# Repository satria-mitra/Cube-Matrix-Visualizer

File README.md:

# Cube-Matrix Visualizer

To see how Cube Matrix works, please visit our [youtube channel](https://www.youtube.com/watch?v=XeQNfcWp1Bc)

## What is Cube-Matrix Visualizer?

Cube-Matrix Visualizer creatively connects the fields of IoT (Internet of Things) technology and art, aiming to create a data visualization device that meets the complex needs of contemporary society. Currently, the device focuses on reacting to changes in humidity, temperature and carbon dioxide concentration with a series of artistic LED animations. In the future, the team will provide OTA (over-the-air) services to upgrade the functionality of the device and enable broader data visualization through more captivating animations.

## Why is Cube-Matrix Visualizer Useful? 

In an era oversaturated with data, the Cube-Matrix Visualizer emerges as a beacon of innovation, merging the practicality of IoT technology with the sublime beauty of art. This fusion presents a unique advantage: making data not only accessible but also aesthetically pleasing, transforming mundane statistics into captivating visual stories.

### Artistry and Technology Combined

The Cube-Matrix Visualizer stands apart through its artistic approach to data visualization. Each LED animation is meticulously crafted, not just for clarity, but to evoke emotion and appreciation for the beauty inherent in data. The device acts as a living canvas, where pixels of light paint the ever-changing tapestry of our environment's data.

### Tailored to the Modern Aesthetic

Designed with modern sensibilities in mind, the Cube-Matrix Visualizer is more than a functional device—it's a piece of art that complements any space. Its sleek design and dynamic visual output offer a dual function: enhancing room aesthetics while providing valuable environmental insights. It's an innovative way to integrate technology into our lives without sacrificing style or comfort.

### Engaging Visual Experience

Beyond mere decoration, the Cube-Matrix Visualizer engages its users on a sensory level. The visualizations are designed not only to inform but to mesmerize, creating an immersive experience that turns data observation into a moment of zen. It encourages users to interact with and reflect on their environmental conditions, fostering a deeper connection between the user and their surroundings.

### A Canvas for Future Possibilities

The promise of OTA updates opens a realm of future possibilities, where the device's artistry and functionality evolve together. New data visualizations can be introduced, offering fresh perspectives and insights, and keeping the user's experience vibrant and current. This commitment to growth ensures that the Cube-Matrix Visualizer remains not only a tool for today but a lasting piece of art that continues to enrich lives.

## Market analysis

We are a small independent entrepreneurial company. Our product is an LED cube system that can visualize the air quality data (including CO2 concentration, temperature, humidity) collected by the sensor using an animation played by the LED cube.  This system uses an independent power supply and a wide voltage design, and can be used directly in most areas of the world. Users can use the buttons on the product base to switch animation modes and display different data. The cost of our product, without taking into account labor costs, is 126 pounds. It takes 24 hours of work for this team member to complete this product. If you consider London wage standards, the total cost is approximately 366 pounds, which is what we need solved problem.
Our target market is technology enthusiasts, education fields, and high-consumption groups. Our products will be crowdfunded on kickstarter.
Our opponents mainly fall into two categories. One is traditional LED cube kits, which are cheaper but cannot provide air quality detection functions. At the same time, they rarely sell finished products, which poses challenges to users’ technical capabilities and time. In addition, such products do not have the ability to interact with users. The other category is traditional air quality detectors, with similar accuracy, they are also cheaper, but they do not have furniture/decoration capabilities and lack the artistic expression of this product.
We will also provide free ota services to crowdfunding users to ensure the rights and interests of crowdfunding users.
Our current market areas are Europe and North America.

### SWOT.
- Advantage
LED CUBE with integrated air quality detection is a pioneering solution in the technology market, offering the dual functionality of air quality detection and visual display via an LED cube. This fusion of innovations not only differentiates the product but also captures a niche market consisting of technology enthusiasts, the education sector and high-spending groups. A significant advantage of this product is that users can interact with the product by changing animation modes and displaying various data, thus enhancing the overall user experience. Additionally, providing over-the-air (OTA) updates to crowdfunding users signifies our commitment to product longevity and customer satisfaction.

- Weakness
Conversely, the product's market penetration may be hampered by its high production costs (approximately £366), placing it in a higher price range, which may limit its acceptance by a wider audience. The production process for each unit requires 24 hours of labor, which not only drives up costs and selling prices, but also cuts production capacity. Furthermore, relying on crowdfunding to enter the market creates financial uncertainty, as access to funds in this way depends on the dynamics of crowdfunding platforms and investor interest.

- Opportunities
As people's living standards improve, people's awareness and concern about air quality in residential and office environments continues to grow, providing important opportunities for market expansion. By finding foundries to reduce costs and selling prices, and upgrading product features, these measures will tap a wider audience and stimulate market growth. Strategic alliances with educational institutions or environmental organizations can open up new avenues of market penetration and enhance brand credibility.

- Threaten
Although this product has good prospects, it still faces severe competition. These threats come from traditional LED cube kits and air quality detectors, which despite their limited functionality compared to the author's team's products, appeal to consumers through lower prices. Additionally, there is a risk that a saturation of similar products with imitators may dilute the uniqueness of the product. Economic fluctuations further exacerbate these threats, as a recession may reduce the disposable income of high-spending groups and reduce their interest in purchasing such products.

In addition, this group introduces value chain analysis here. Through the exploration of main activities and supporting activities, this analysis describes how to add value and minimize costs, thereby enhancing the product's competitive advantage in the global market.

### Main activities
-Inbound logistics
The initial stage of the value creation process: procuring high-quality sensors and LEDs from reputable suppliers to ensure product quality. At the same time, efficient inventory management is required to minimize storage costs and avoid stock-outs, thereby maintaining a seamless production process.

-Operations
The assembly of the LED cube system is a critical operation. The development of custom firmware for animated data display is at the heart of the product's uniqueness. Strict quality assurance processes are also implemented to meet the safety and performance standards of the regions in which they are sold.

-Outbound logistics
Strategic packaging of products not only ensures their protection during transportation, but also focuses on an environmentally friendly ethos. Logistics partners are selected with a focus on reliability and cost-effectiveness to facilitate global delivery capabilities.

-Marketing and Sales
Use social media, technology blogs and online forums to engage digital marketing strategies to attract the interest of technology enthusiasts and the education sector. Prepare your Kickstarter campaign carefully, aiming to emphasize the product's unique value proposition while seeking partnerships with educational institutions and environmental organizations to increase awareness of the product.

-Serve
Increase customer satisfaction and product longevity by providing after-sales support with comprehensive customer service for setup, usage and troubleshooting, as well as OTA updates for firmware enhancements and feature additions.

### Support activities
-Purchase
Negotiations with suppliers have a dual goal: to secure the best price without compromising quality, and to work with suppliers who can support scalable solutions as volumes increase.

-Technology development
The commitment to ongoing research and development is evident, with the goals of improving product performance, reducing production costs and incubating new features. Software development investments are aimed at refining the user interface and expanding functionality.

-Human resource Management
We are committed to training our teams in efficient production techniques and exemplary customer service, cultivating a culture full of innovation and continuous improvement.

-Infrastructure
The management of the overall operating structure focuses on financial management, legal support and administrative functions. We envisioned a scalable infrastructure capable of adapting to growing business needs, such as flexible IT systems and workspaces.

### Identify areas for improvement and cost reduction
Operational efficiency is targeted to improve, with potential strategies including automation and improved assembly techniques to reduce significant production time. Production scaling is considered a means to exploit economies of scale, thereby reducing unit costs and enhancing market competitiveness. Diversification of the supplier base is recommended to reduce risk and possibly cost through competitive sourcing. In addition, digital marketing efforts will be strengthened to use analytics as a tool to increase focus on ideal customer segments to optimize conversion rates.

## Getting Started

The Cube-Matrix Visualizer is available as a finished product. To get started:

1. Place an order and inspect the product upon arrival to ensure it's in good condition.
2. Connect the device to a power source. It's designed to support a wide range of voltages, making it accessible to users in various locations without the need for additional transformers. However, users with specific electricity requirements should use appropriate converters.
3. Once powered, the Cube will activate. Please allow a brief period for its sensors to adjust to optimal working conditions.
4. To cycle through different LED animations, simply press the button located on the front base of the device. Animations will change in sequence.

Now, you can assemble your own Cube-Matrix. To make your own cube, please follow the steps below:

1. Clone the Repository: git clone https://github.com/satria-mitra/Cube-Matrix.git
2. Hardware Setup: Assemble the Cube Matrix using the provided list of components and assembly instructions found in the Hardware folder.
3. Software Configuration: Navigate to the Software folder and follow the setup instructions to install necessary libraries and upload the code to your microcontroller.
4. Running Cube Matrix: Power up the device and use the button interface to toggle between different environmental data visualizations.

**Cube making steps**  
1. Use 3D printer to print two solder holders（solder holders/Holder-3.stl）.
   
3. Splice the two holders together, place the rgb LED on the holder and solder the data pin (data in to data out) between the two LEDs.
   
4. Cut and straighten the copper wire and place the copper wire on the groove of the holder,then solder rgb led and copper wires according to the schematic diagram to make eight led layers, and power up to test each layer.
   
6. Laser cut four cube holders, then use the holders to support the layers to build the cube and solder the ground, power and data pins for each layer（Pay attention to the data pin connection method of each layer, data in must be connected to data out.）.
   
8. Use Adafruit Feather M0 Doard to connect the cube, connect the ground and power supply normally, and connect the data in of the bottom layer to the D6 pin of the board.
9. Upload the (Scripts/Final_code/Cube_Final.ino)code to the board, and the cube will display three animations in a loop.

## Getting Help

Owners of the Cube-Matrix Visualizer will receive a comprehensive manual detailing operational guidance and troubleshooting tips. Further assistance is available through several channels:

- **Email Support:** For direct inquiries, contact our customer service at Cube-Matrix-Visualizer@gmail.com.
- **GitHub Repository:** Feel free to post questions or feedback in the issues section of our GitHub repository.
- **Future Online Support:** We plan to launch a dedicated website offering an enhanced support function for an improved user experience.

For more direct assistance, you can also reach out to our team members via GitHub profiles linked in the Contributors section

## Contributors
Cube Matrix is maintained and contributed to by a dedicated team of students from the Connected Environments course at CASA. Our team members are
1. [Satria Utama ](https://github.com/satria-mitra)
2. [Guandi Chen](https://github.com/grandy0831)
3. [Huanchao Hong](https://github.com/ChaceHH-H)
4. [Zekun Wang](https://github.com/AntiRain114)

## Design, Development, and Execution
The Cube Matrix project started as an inspiration from a basic LED cube project, evolving into a sophisticated tool for visualizing environmental quality. The project's development journey, from the initial 5x5x5 cube prototype to the advanced 8x8x8 design, showcases our commitment to innovation and user-centric design.  

## Key Features
Environmental Monitoring: Measures temperature, humidity, and CO2 levels.
Dynamic Visual Display: Uses animations to display IEQ data, making it intuitive.
Educational Tool: Helps users understand the impact of IEQ on health and well-being.
For a comprehensive overview of the design process, technical challenges, and our solutions, please refer to the Documentation folder, which includes detailed design documents and technical drawings.

## License
This project is licensed under the MIT License - see the LICENSE file for details.

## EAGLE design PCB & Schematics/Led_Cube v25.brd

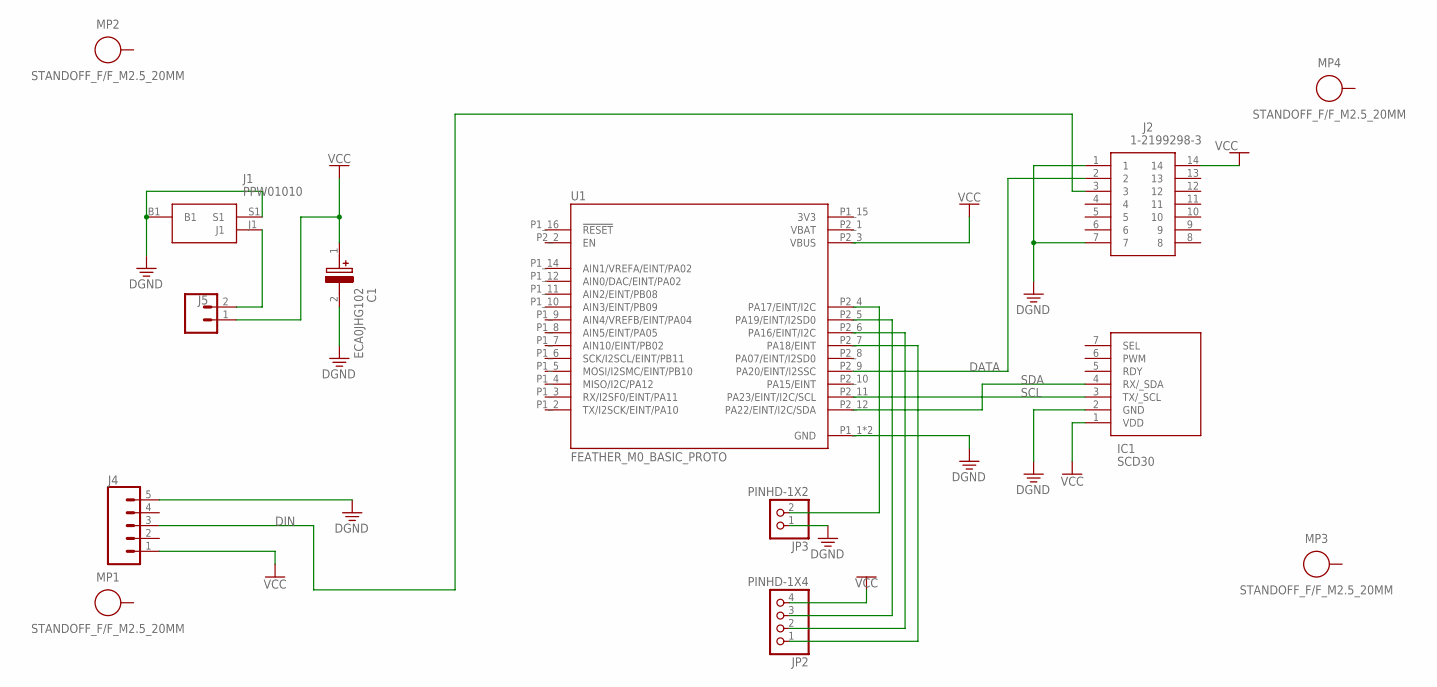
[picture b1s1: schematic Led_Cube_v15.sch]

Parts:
C1: ECA0JHG102; CAPPRD350W65D800H1250
IC1: SCD30
J1: PPW01010
J2: 1-2199298-3; DIPS762W70P254L1778H510Q14N
J4: CONN_05PTH; 1X05
J5: CONN_02; 1X02
JP2: PINHD-1X4; 1X04
JP3: PINHD-1X2; 1X02
MP1, MP2, MP3, MP4: STANDOFF_F/F_M2.5_20MM; STANDOFF_HEX_FEMALE_500X2000_M2.5X0.45_MTGP755H270
U1: FEATHER_M0_BASIC_PROTO; MODULE_FEATHER_M0_BASIC_PROTO

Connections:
3V3: U1.P1_15 (3V3)
BLUE: JP2.3, U1.P2_5 (PA19/EINT/I2SD0)
DATA: J2.2, U1.P2_9 (PA20/EINT/I2SSC)
DGND: C1.2 (-), IC1.2 (GND), J1.B1, J1.S1, J2.1, J2.7, J4.5, JP3.1, U1.P1_1 (GND), U1.P1_13 (GND)
DIN: J2.3, J4.3
GREEN: JP2.2, U1.P2_6 (PA16/EINT/I2C)
unnamed: J1.J1, J5.2
RED: JP2.1, U1.P2_7 (PA18/EINT)
SCL: IC1.3 (TX/_SCL), U1.P2_11 (PA23/EINT/I2C/SCL)
SDA: IC1.4 (RX/_SDA), U1.P2_12 (PA22/EINT/I2C/SDA)
SW1: JP3.2, U1.P2_4 (PA17/EINT/I2C)
VBAT: U1.P2_1 (VBAT)
VCC: C1.1 (+), IC1.1 (VDD), J2.14, J4.1, J5.1, JP2.4, U1.P2_3 (VBUS)

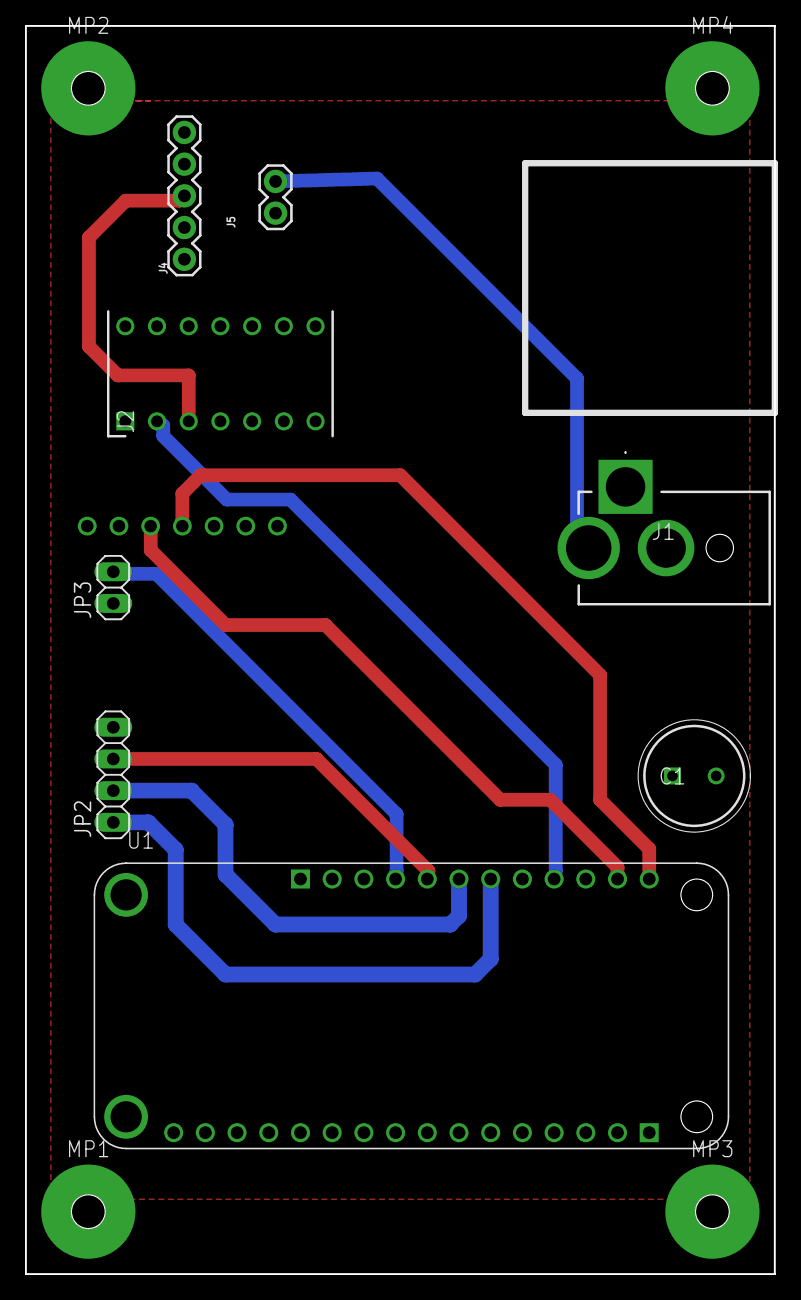
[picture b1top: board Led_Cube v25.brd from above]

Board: 2 copper layers, 60.0 x 100.0 mm, 13 parts (1 on the bottom side), 11 nets.

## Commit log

2024-01-22 Update LICENSE
2024-01-22 upload crits ppt
2024-03-01 upload pcb
2024-03-01 upload git ignore
2024-03-01 upload case design
2024-03-01 upload PCB 3d model
2024-03-01 new test code
2024-03-08 Create Animation Code
2024-03-08 Update rain1.ino
    The rain 1 code is a simple animation of falling raindrops
2024-03-08 update rain animation
2024-03-08 Updated the gradient animation of the code.
    After the raindrops fall, they will change from dark blue to light blue.
2024-03-08 Updated the gradient animation of the code
    the accumulation of raindrops changes from dark blue to light blue
2024-03-08 Add files via upload
    Falling raindrops and accumulated water both have a gradient from dark to light blue depending on their height within the cube.
2024-03-08 Add files via upload
    Update the code, the top layer is dark blue and the bottom layer is light blue
2024-03-08 Create RainAM.ino
    new Rain
2024-03-08 Create button_rgb.ino
    Button
2024-03-08 Create led-cube-test-1.ino
    main
2024-03-09 firework animation
2024-03-09 Added animation of fireworks falling
2024-03-09 Update led-cube-test-1.ino
    3/9-update button code
2024-03-09 button
2024-03-11 update
    update
2024-03-16 upload final code
2024-03-18 upload 3d parts and cutting components
2024-03-18 upload .gitignore mac files
2024-03-18 upload schematics and cam files
2024-03-18 rearranged files
2024-03-18 upload crits pdf
2024-03-28 Plan changes, production steps
2024-04-23 [ImgBot] Optimize images
    /LED schematic.png -- 75.19kb -> 36.51kb (51.45%)

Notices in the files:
parts and their libraries:
SparkFun-Connectors: Licensing: Creative Commons ShareAlike 4.0 International - https://creativecommons.org/licenses/by-sa/4.0
